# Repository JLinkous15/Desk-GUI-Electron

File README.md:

See Figma mockups here:
https://www.figma.com/design/cUYNgPsbwDiiWW71hespAt/Untitled

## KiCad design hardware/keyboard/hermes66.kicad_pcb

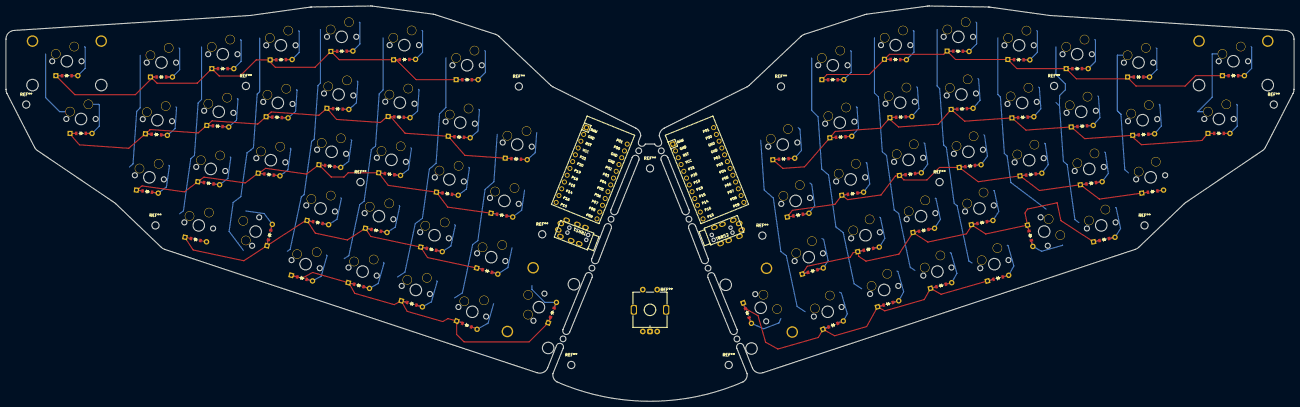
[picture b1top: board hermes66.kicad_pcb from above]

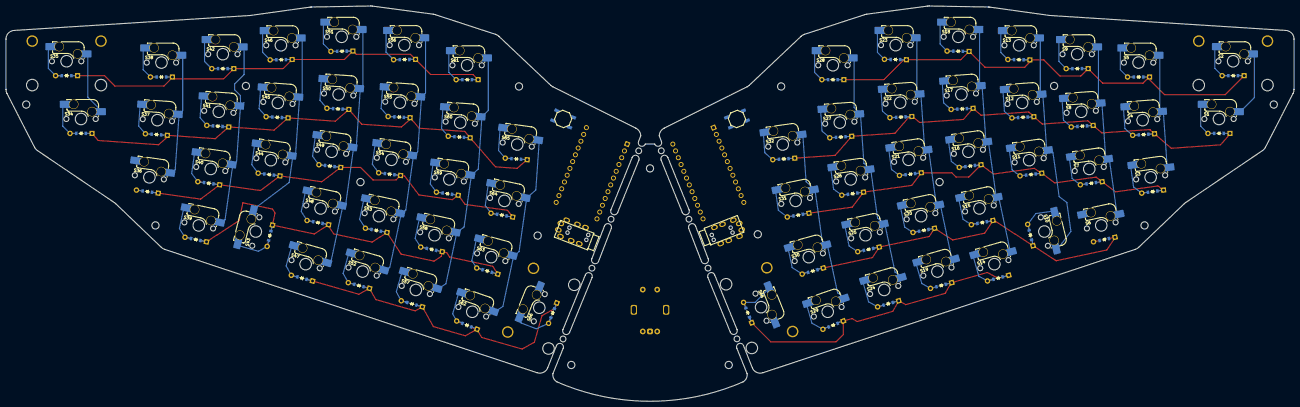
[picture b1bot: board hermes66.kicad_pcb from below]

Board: 2 copper layers, 446.3 x 137.0 mm, 138 parts (68 on the bottom side), 99 nets.

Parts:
B1, B2: SW_TACT_ALPS_SKQGABE010
D1, D2, D3, D4, D5, D6, D7, D8, D9, D10, D11, D12, D13, D14, D15, D16, D17, D18, D19, D20, D21, D22, D23, D24, D25, D26, D27, D28, D29, D30, D31, D32, D34, D35, D36, D37, D38, D39, D40, D41, D42, D43, D44, D45, D46, D47, D48, D49, D50, D51, D52, D53, D54, D55, D56, D57, D58, D59, D60, D61, D62, D63, D64, D65, D66, D66#2: ComboDiode
MCU1, MCU2: ProMicro
S1, S10, S34, S43: SW_MX_HS_CPG151101S11_1.5u
S2, S3, S4, S5, S6, S7, S8, S9, S11, S12, S13, S14, S15, S16, S17, S18, S19, S20, S21, S22, S23, S24, S25, S26, S27, S28, S29, S30, S31, S32, S35, S36, S37, S38, S39, S40, S41, S42, S44, S45, S46, S47, S48, S49, S50, S51, S52, S53, S54, S55, S56, S57, S58, S59, S60, S61, S62, S63, S64, S65, S66, S66#2: SW_MX_HS_CPG151101S11_1u
TRRS1, TRRS2: MJ-4PP-9_Reversible; CON_MJ-4PP-9_Reversible

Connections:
GND: B1.1, B2.1, MCU1.2, MCU1.15, MCU1.16, MCU2.2, MCU2.15, MCU2.16
P0: MCU1.14, MCU2.14
P1: MCU1.13, MCU2.13
P2: S1.1, S2.1, S34.1, S35.1
P3: S3.1, S4.1, S5.1, S36.1, S37.1, S38.1
P4: S6.1, S7.1, S8.1, S9.1, S39.1, S40.1, S41.1, S42.1
P5: S10.1, S11.1, S12.1, S13.1, S43.1, S44.1, S45.1, S46.1
P6: S14.1, S15.1, S16.1, S17.1, S18.1, S47.1, S48.1, S49.1, S50.1, S51.1
P7: S19.1, S20.1, S21.1, S22.1, S23.1, S52.1, S53.1, S54.1, S55.1, S56.1
P8: S24.1, S25.1, S26.1, S27.1, S28.1, S57.1, S58.1, S59.1, S60.1, S61.1
P9: MCU1.24, MCU2.24, S29.1, S30.1, S31.1, S32.1, S62.1, S63.1, S64.1, S65.1
P10: MCU1.12, MCU2.12
P14: MCU1.10, MCU2.10
P15: D14.1, D19.1, D24.1, D29.1, D47.1, D52.1, D57.1, D62.1, D66.1, D66#2.1
P16: MCU1.11, MCU2.11
P18: D6.1, D10.1, D15.1, D20.1, D25.1, D30.1, D39.1, D43.1, D48.1, D53.1, D58.1, D63.1
P19: D3.1, D7.1, D11.1, D16.1, D21.1, D26.1, D31.1, D36.1, D40.1, D44.1, D49.1, D54.1, D59.1, D64.1
P20: D1.1, D4.1, D8.1, D12.1, D17.1, D22.1, D27.1, D32.1, D34.1, D37.1, D41.1, D45.1, D50.1, D55.1, D60.1, D65.1
P21: D2.1, D5.1, D9.1, D13.1, D18.1, D23.1, D28.1, D35.1, D38.1, D42.1, D46.1, D51.1, D56.1, D61.1
RAW: MCU1.1, MCU2.1
RST: B1.2, B2.2, MCU1.3, MCU2.3
VCC: MCU1.4, MCU2.4
collumns_inner: MCU1.23, MCU2.23
columns_extra-outer: MCU1.17, MCU2.17
columns_index: MCU1.22, MCU2.22
columns_middle: MCU1.21, MCU2.21
columns_outer: MCU1.18, MCU2.18
columns_pinky: MCU1.19, MCU2.19
columns_ring: MCU1.20, MCU2.20
extra-outer_num: D2.2, S2.2
extra-outer_top: D1.2, S1.2
index_bottom: D20.2, S20.2
index_home: D21.2, S21.2
index_mod: D19.2, S19.2
index_num: D23.2, S23.2
index_top: D22.2, S22.2
inner_bottom: D25.2, S25.2
inner_home: D26.2, S26.2
inner_mod: D24.2, S24.2
inner_num: D28.2, S28.2
inner_top: D27.2, S27.2
middle_bottom: D15.2, S15.2
middle_home: D16.2, S16.2
middle_mod: D14.2, S14.2
middle_num: D18.2, S18.2
middle_top: D17.2, S17.2
mirror_extra-outer_num: D35.2, S35.2
mirror_extra-outer_top: D34.2, S34.2
mirror_index_bottom: D53.2, S53.2
mirror_index_home: D54.2, S54.2
mirror_index_mod: D52.2, S52.2
mirror_index_num: D56.2, S56.2
mirror_index_top: D55.2, S55.2
mirror_inner_bottom: D58.2, S58.2
mirror_inner_home: D59.2, S59.2
mirror_inner_mod: D57.2, S57.2
mirror_inner_num: D61.2, S61.2
mirror_inner_top: D60.2, S60.2
mirror_middle_bottom: D48.2, S48.2
mirror_middle_home: D49.2, S49.2
mirror_middle_mod: D47.2, S47.2
mirror_middle_num: D51.2, S51.2
mirror_middle_top: D50.2, S50.2
mirror_outer_home: D36.2, S36.2
mirror_outer_num: D38.2, S38.2
mirror_outer_top: D37.2, S37.2
mirror_pinky_bottom: D39.2, S39.2
mirror_pinky_home: D40.2, S40.2
mirror_pinky_num: D42.2, S42.2
mirror_pinky_top: D41.2, S41.2
mirror_ring_bottom: D43.2, S43.2
mirror_ring_home: D44.2, S44.2
mirror_ring_num: D46.2, S46.2
mirror_ring_top: D45.2, S45.2
mirror_thumb_bottom: D63.2, S63.2
mirror_thumb_home: D64.2, S64.2
mirror_thumb_mod: D62.2, S62.2
mirror_thumb_thumb: D66.2, D66#2.2, S66.2, S66#2.2
mirror_thumb_top: D65.2, S65.2
outer_home: D3.2, S3.2
outer_num: D5.2, S5.2
outer_top: D4.2, S4.2
pinky_bottom: D6.2, S6.2
pinky_home: D7.2, S7.2
pinky_num: D9.2, S9.2
pinky_top: D8.2, S8.2
ring_bottom: D10.2, S10.2
ring_home: D11.2, S11.2
ring_num: D13.2, S13.2
ring_top: D12.2, S12.2
row_bottom: MCU1.8, MCU2.8
row_home: MCU1.7, MCU2.7
row_mod: MCU1.9, MCU2.9
row_num: MCU1.5, MCU2.5
row_top: MCU1.6, MCU2.6
thumb_bottom: D30.2, S30.2
thumb_home: D31.2, S31.2
thumb_mod: D29.2, S29.2
thumb_top: D32.2, S32.2

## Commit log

2024-06-13 bootstrapping complete,
2024-06-17 Finally decided on method for bootstrapping.
2024-06-18 timer working in reverse. needs lots of cleanup
2024-06-18 Timer angles work as expected
2024-06-19 styling changes to nav, bootstrap dialogs, began workflow for timer selections, cleaned up code.
2024-06-19 select and resize to appropriate monitor
2024-06-20 successfully scaffolded entire app with cleanup
2024-06-20 cleaned up imports, types, and code styling
2024-06-22 updates to electron environment, starting todos.
2024-06-23 pomodoro timer working.
2024-06-23 Custom timer bug fixed. Styling still needed, but fine for now.
2024-06-23 prettier and final reset on pomodoro timer
2024-06-24 markdown installed and eat the frog setup.
2024-06-25 setup get request to local files
2024-07-01 big file structure adjustment.
2024-07-02 path to notes decided
2024-07-03 okay ready to work
2024-07-07 new main
2024-07-07 small style changed
2024-07-14 hardware work and readme stuff
2024-07-15 Working IPC with zero errors
2024-07-17 read finished
2024-07-17 rectifying PR deletion
2024-08-03 markdown editor replaces with rich text editor.
2024-08-04 Move tiptap toolbar to bubble and float menu. Added query through IPC for polygon.io query.
2024-08-07 some get requests scaffolded across multiple processes
2024-08-27 commit test
